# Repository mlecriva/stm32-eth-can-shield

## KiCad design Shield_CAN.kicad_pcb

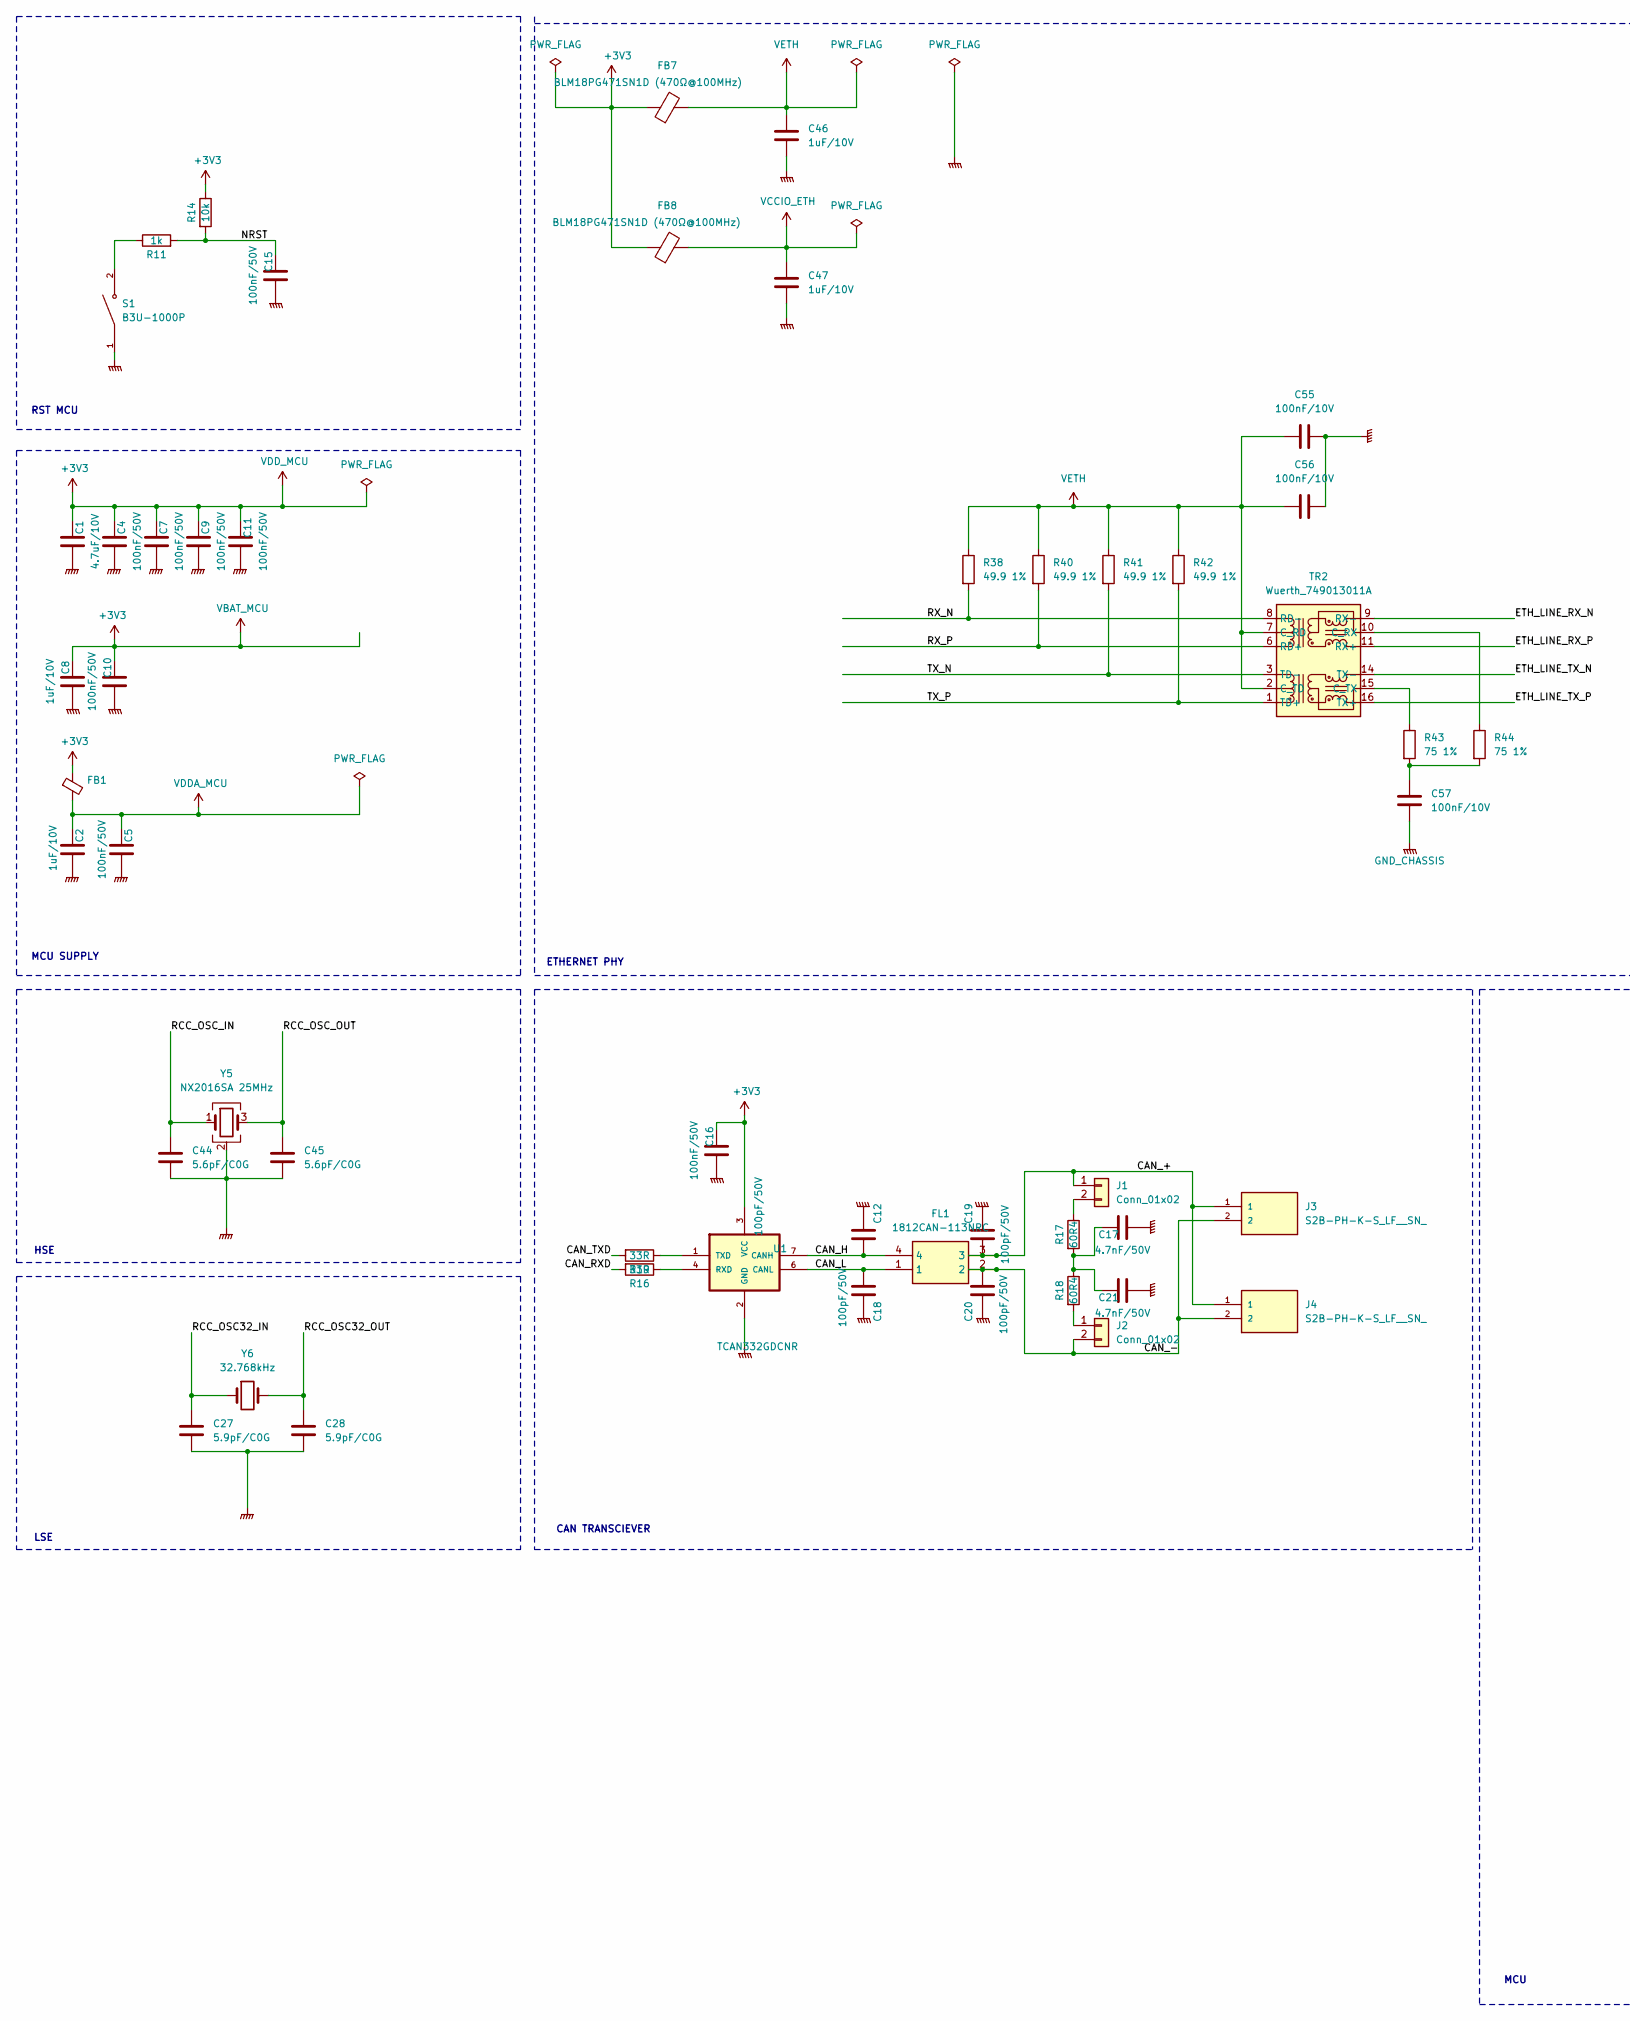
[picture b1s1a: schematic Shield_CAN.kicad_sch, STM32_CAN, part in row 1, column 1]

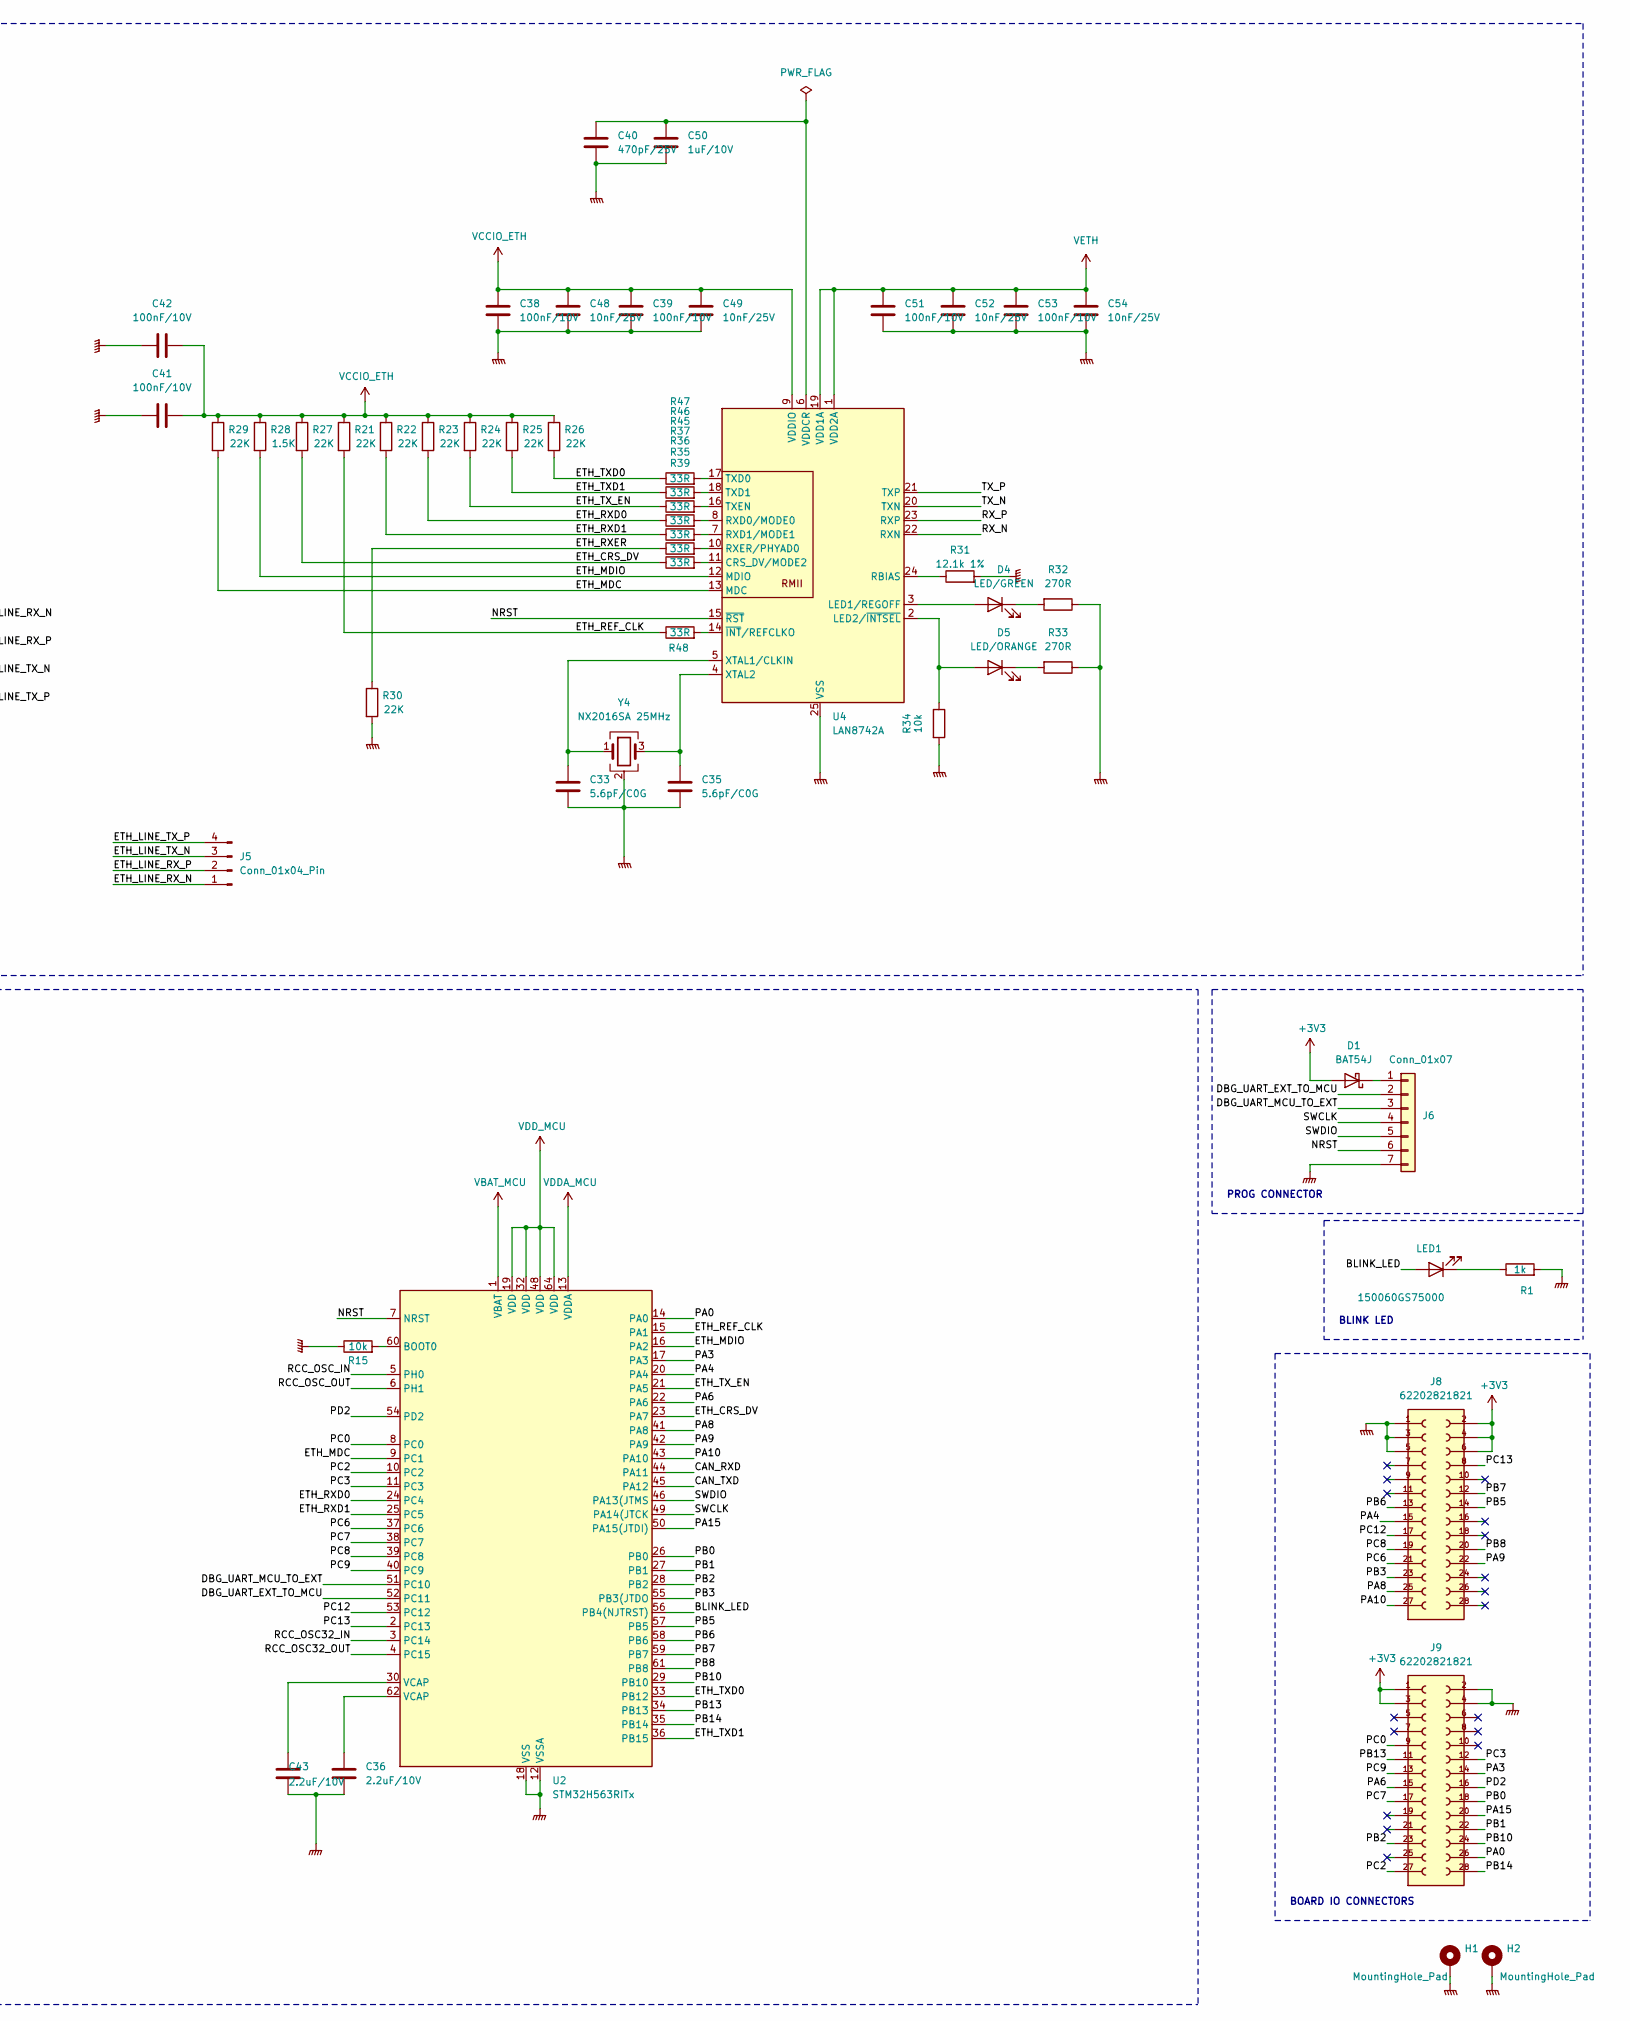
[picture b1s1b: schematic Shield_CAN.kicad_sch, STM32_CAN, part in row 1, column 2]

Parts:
C1: 4.7uF/10V; C_0402_1005Metric; Mfr. Part # GRM155R61A475KEAAD; Digikey_Code 1276-6462-1-ND
C2, C8, C46, C47: 1uF/10V; C_0402_1005Metric; Mfr. Part # CL05A105KP5NNNC; Digikey_Code 445-5138-1-ND
C4, C5, C7, C9, C10, C11, C15, C16: 100nF/50V; C_0402_1005Metric; Mfr. Part # GRM155R71H104KE14D; Digikey_Code 490-GRM155R61H104ME14DCT-ND
C12, C18, C19, C20: 100pF/50V; C_0402_1005Metric; Mfr. Part # C0402C101K5RACAUTO; Digikey_Code 732-7550-1-ND
C17, C21: 4.7nF/50V; C_0402_1005Metric; Mfr. Part # 0402B472K500NT; Digikey_Code 478-KGM05AR71H472KHCT-ND
C27, C28: 5.9pF/C0G; C_0402_1005Metric; Mfr. Part # GJM1555C1H5R9CB01D; LCSC Part # C3846240
C33, C35, C44, C45: 5.6pF/C0G; C_0402_1005Metric; Mfr. Part # GRM1555C1H5R6BA01D; LCSC Part # C76976
C36, C43: 2.2uF/10V; C_0402_1005Metric; Mfr. Part # GRM155Z71A225KE01D; LCSC Part # C2997286
C38, C39, C41, C42, C51, C53, C55, C56, C57: 100nF/10V; C_0402_1005Metric; Mfr. Part # GRM155R71A104KA01D; Digikey_Code 490-GRM155R61H104ME14DCT-ND
C40: 470pF/25V; C_0402_1005Metric; Mfr. Part # CC0402KRX7R8BB471; LCSC Part # C541387
C48, C49, C52, C54: 10nF/25V; C_0402_1005Metric; Mfr. Part # C77013; LCSC Part # C77013
C50: 1uF/10V; C_0402_1005Metric; Mfr. Part # CL05A105KP5NNNC; LCSC Part # C14445
D1: BAT54J; D_SOD-323F; Mfr. Part # BAT54J,115; Digikey_Code 1727-4818-1-ND
D4: LED/GREEN; LED_0603_1608Metric; Mfr. Part # A-SP192DGHC-C01-4T; LCSC Part # C19171301
D5: LED/ORANGE; LED_0603_1608Metric; Mfr. Part # A-SP192DS1C-A01-4T; LCSC Part # C19171353
FB1, FB7: BLM18PG471SN1D (470Ω@100MHz); L_0603_1608Metric; Mfr. Part # BLM18PG600SN1D; Digikey_Code 1934-1469-1-ND
FB8: BLM18PG471SN1D (470Ω@100MHz); L_0603_1608Metric; Mfr. Part # BLM18PG600SN1D; LCSC Part # C85834
FL1: 1812CAN-113NRC; 1812CAN113NRC; Manufacturer_Part_Number 1812CAN-113NRC; Mouser Part Number 994-1812CAN-113NRC
H1, H2: MountingHole_Pad; MountingHole_3mm_Pad
J1, J2: Conn_01x02; PinHeader_1x02_P2.54mm_Vertical; Mfr. Part # P125-1102A0CS116A1; Digikey_Code 732-5315-ND
J3, J4: S2B-PH-K-S_LF__SN_; JST_PH_B2B-PH-K_1x02_P2.00mm_Vertical; Mfr. Part # HDGC2001WV-2P; Digikey_Code 455-1719-ND
J5: Conn_01x04_Pin; Molex_PicoBlade_53047-0410_1x04_P1.25mm_Vertical
J6: Conn_01x07; Molex_PicoBlade_53047-0710_1x07_P1.25mm_Vertical
J8, J9: 62202821821; Mfr. Part # PM127-2-14-Z-4.3-G0; Digikey_Code 732-62202821821-ND
LED1: 150060GS75000; LED_0603_1608Metric; Manufacturer_Part_Number 150060GS75000; Mouser Part Number 710-150060GS75000
R1, R11: 1k; R_0402_1005Metric; Mfr. Part # 0402WGF1001TCE; Digikey_Code YAG3525CT-ND
R14, R15, R34: 10k; R_0402_1005Metric; Mfr. Part # 0402WGF1002TCE; Digikey_Code CR0402-FX-1002GLFCT-ND
R16, R19, R35, R36, R37, R39, R45, R46, R47, R48: 33R; R_0402_1005Metric; Mfr. Part # 0402WGF330JTCE; Digikey_Code 311-33.0LRCT-ND
R17: 60R4; R_0402_1005Metric; Mfr. Part # 0402WGF604JTCE; Digikey_Code 13-RT0805FRE0760R4LCT-ND
R18: 60R4; R_0402_1005Metric; Mfr. Part # 0402WGF604JTCE; Digikey_Code 311-33.0LRCT-ND
R21, R22, R23, R24, R25, R26, R27, R29, R30: 22K; R_0402_1005Metric; Mfr. Part # RC0402FR-0722KL; LCSC Part # C82868
R28: 1.5K; R_0402_1005Metric; Mfr. Part # 0402WGF1501TCE; LCSC Part # C25867
R31: 12.1k 1%; R_0402_1005Metric; Mfr. Part # RTT021212FTH; LCSC Part # C102786
R32, R33: 270R; R_0402_1005Metric; Mfr. Part # CR0402FF2700G; Digikey_Code 311-33.0LRCT-ND
R38, R40, R41, R42: 49.9 1%; R_0402_1005Metric; Mfr. Part # 0402WGF499JTCE; LCSC Part # C25120
R43: 75 1%; R_0402_1005Metric; Mfr. Part # 0402WGF750JTCE; LCSC Part # C25133
R44: 75 1%; R_0402_1005Metric; Mfr. Part # 0402WGF750JTCE; Digikey_Code 311-33.0LRCT-ND
S1: B3U-1000P; SW_B3U-1000P; Mfr. Part # B3U-1000P; LCSC Part # C231329
TR2: Wuerth_749013011A; Transformer_Ethernet_Wuerth_749013011A; Mfr. Part # 749013011A; LCSC Part # C7193798
U1: TCAN332GDCNR; SOT65P280X145-8N; Mfr. Part # TCAN332GDCNR; Digikey_Code 311-33.0LRCT-ND
U2: STM32H563RITx; LQFP-64_10x10mm_P0.5mm; Mfr. Part # STM32H563RIT6; LCSC Part # C20619634
U4: LAN8742A; VQFN-24-1EP_4x4mm_P0.5mm_EP2.5x2.5mm_ThermalVias; Mfr. Part # LAN8742A-CZ-TR; LCSC Part # C621424
Y4, Y5: NX2016SA 25MHz; Crystal_SMD_2016-4Pin_2.0x1.6mm; Mfr. Part # NX2016SA-25MHZ-STD-CZS-2; LCSC Part # C843258
Y6: 32.768kHz; Crystal_SMD_2012-2Pin_2.0x1.2mm_HandSoldering; Mfr. Part # NX2012SA_32.768K_STD-MUB-1; LCSC Part # C500343

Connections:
+3V3: C1.1, C4.1, C7.1, C8.1, C9.1, C10.1, C11.1, C16.1, D1.2 (A), FB1.1, FB7.1, FB8.1, J8.2, J8.4, J8.6, J9.1, J9.3, R14.1, U1.3 (VCC), U2.1 (VBAT), U2.19 (VDD), U2.32 (VDD), U2.48 (VDD), U2.64 (VDD)
/BLINK_LED: LED1.2 (A), U2.56 (PB4(NJTRST))
/CAN_+: C19.1, FL1.3, J1.1, J3.1, J4.1
/CAN_-: C20.1, FL1.2, J2.2, J3.2, J4.2
/CAN_H: C12.1, FL1.4, U1.7 (CANH)
/CAN_L: C18.1, FL1.1, U1.6 (CANL)
/CAN_RXD: R16.2, U2.44 (PA11)
/CAN_TXD: R19.2, U2.45 (PA12)
/DBG_UART_EXT_TO_MCU: J6.2, U2.52 (PC11)
/DBG_UART_MCU_TO_EXT: J6.3, U2.51 (PC10)
/ETH_CRS_DV: R27.2, R47.1, U2.23 (PA7)
/ETH_LINE_RX_N: J5.1, TR2.9 (RX-)
/ETH_LINE_RX_P: J5.2, TR2.11 (RX+)
/ETH_LINE_TX_N: J5.3, TR2.14 (TX-)
/ETH_LINE_TX_P: J5.4, TR2.16 (TX+)
/ETH_MDC: R29.2, U2.9 (PC1), U4.13 (MDC)
/ETH_MDIO: R28.2, U2.16 (PA2), U4.12 (MDIO)
/ETH_REF_CLK: R21.2, R48.1, U2.15 (PA1)
/ETH_RXD0: R23.2, R39.1, U2.24 (PC4)
/ETH_RXD1: R22.2, R45.1, U2.25 (PC5)
/ETH_RXER: R30.1, R46.1
/ETH_TXD0: R26.2, R35.1, U2.33 (PB12)
/ETH_TXD1: R25.2, R36.1, U2.36 (PB15)
/ETH_TX_EN: R24.2, R37.1, U2.21 (PA5)
/NRST: C15.1, J6.6, R11.2, R14.2, U2.7 (NRST), U4.15 (~RST)
/PA0: J9.26, U2.14 (PA0)
/PA3: J9.14, U2.17 (PA3)
/PA4: J8.15, U2.20 (PA4)
/PA6: J9.15, U2.22 (PA6)
/PA8: J8.25, U2.41 (PA8)
/PA9: J8.22, U2.42 (PA9)
/PA10: J8.27, U2.43 (PA10)
/PA15: J9.20, U2.50 (PA15(JTDI))
/PB0: J9.18, U2.26 (PB0)
/PB1: J9.22, U2.27 (PB1)
/PB2: J9.23, U2.28 (PB2)
/PB3: J8.23, U2.55 (PB3(JTDO)
/PB5: J8.14, U2.57 (PB5)
/PB6: J8.13, U2.58 (PB6)
/PB7: J8.12, U2.59 (PB7)
/PB8: J8.20, U2.61 (PB8)
/PB10: J9.24, U2.29 (PB10)
/PB13: J9.11, U2.34 (PB13)
/PB14: J9.28, U2.35 (PB14)
/PC0: J9.9, U2.8 (PC0)
/PC2: J9.27, U2.10 (PC2)
/PC3: J9.12, U2.11 (PC3)
/PC6: J8.21, U2.37 (PC6)
/PC7: J9.17, U2.38 (PC7)
/PC8: J8.19, U2.39 (PC8)
/PC9: J9.13, U2.40 (PC9)
/PC12: J8.17, U2.53 (PC12)
/PC13: J8.8, U2.2 (PC13)
/PD2: J9.16, U2.54 (PD2)
/RCC_OSC32_IN: C27.1, U2.3 (PC14), Y6.1
/RCC_OSC32_OUT: C28.1, U2.4 (PC15), Y6.2
/RCC_OSC_IN: C44.1, U2.5 (PH0), Y5.1
/RCC_OSC_OUT: C45.1, U2.6 (PH1), Y5.3
/RX_N: R38.2, TR2.8 (RD-), U4.22 (RXN)
/RX_P: R40.2, TR2.6 (RD+), U4.23 (RXP)
/SWCLK: J6.4, U2.49 (PA14(JTCK)
/SWDIO: J6.5, U2.46 (PA13(JTMS)
/TX_N: R41.2, TR2.3 (TD-), U4.20 (TXN)
/TX_P: R42.2, TR2.1 (TD+), U4.21 (TXP)
GNDPWR: C1.2, C2.2, C4.2, C5.2, C7.2, C8.2, C9.2, C10.2, C11.2, C12.2, C15.2, C16.2, C17.2, C18.2, C19.2, C20.2, C21.2, C27.2, C28.2, C33.2, C35.2, C36.2, C38.2, C39.2, C40.2, C41.1, C42.1, C43.2, C44.2, C45.2, C46.2, C47.2, C48.2, C49.2, C50.2, C51.2, C52.2, C53.2, C54.2, C55.2, C56.2, H1.1 (1_1), H2.1 (1_1), J6.7, J8.1, J8.3, J8.5, J9.2, J9.4, R1.2, R15.1, R30.2, R31.2, R32.1, R33.1, R34.2, S1.1, U1.2 (GND), U2.12 (VSSA), U2.18 (VSS), U2.31 (VSS), U2.47 (VSS), U2.63 (VSS), U4.25 (VSS), Y4.2 (G), Y4.4 (G), Y5.2 (G), Y5.4 (G)
GND_CHASSIS: C57.1
unnamed: C17.1, C21.1, R17.2, R18.1
unnamed: C36.1, U2.62 (VCAP)
unnamed: C43.1, U2.30 (VCAP)
unnamed: C57.2, R43.2, R44.2
unnamed: D1.1 (K), J6.1
unnamed: D4.2 (A), U4.3 (LED1/REGOFF)
unnamed: D4.1 (K), R32.2
unnamed: D5.2 (A), R34.1, U4.2 (LED2/~INTSEL)
unnamed: D5.1 (K), R33.2
unnamed: J1.2, R17.1
unnamed: J2.1, R18.2
unnamed: LED1.1 (K), R1.1
unnamed: R11.1, S1.2
unnamed: R44.1, TR2.10 (C_RX)
unnamed: R43.1, TR2.15 (C_TX)
unnamed: R16.1, U1.4 (RXD)
unnamed: R19.1, U1.1 (TXD)
unnamed: R15.2, U2.60 (BOOT0)
unnamed: R47.2, U4.11 (CRS_DV/MODE2)
unnamed: R31.1, U4.24 (RBIAS)
unnamed: R39.2, U4.8 (RXD0/MODE0)
unnamed: R45.2, U4.7 (RXD1/MODE1)
unnamed: R46.2, U4.10 (RXER/PHYAD0)
unnamed: R35.2, U4.17 (TXD0)
unnamed: R36.2, U4.18 (TXD1)
unnamed: R37.2, U4.16 (TXEN)
unnamed: C40.1, C50.1, U4.6 (VDDCR)
unnamed: C33.1, U4.5 (XTAL1/CLKIN), Y4.1
unnamed: C35.1, U4.4 (XTAL2), Y4.3
unnamed: R48.2, U4.14 (~INT/REFCLKO)
VCCIO_ETH: C38.1, C39.1, C41.2, C42.2, C47.1, C48.1, C49.1, FB8.2, R21.1, R22.1, R23.1, R24.1, R25.1, R26.1, R27.1, R28.1, R29.1, U4.9 (VDDIO)
VDDA_MCU: C2.1, C5.1, FB1.2, U2.13 (VDDA)
VETH: C46.1, C51.1, C52.1, C53.1, C54.1, C55.1, C56.1, FB7.2, R38.1, R40.1, R41.1, R42.1, TR2.2 (C_TD), TR2.7 (C_RD), U4.1 (VDD2A), U4.19 (VDD1A)

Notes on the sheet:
MCU
HSE
BLINK LED
CAN TRANSCIEVER
RST MCU
BOARD IO CONNECTORS
ETHERNET PHY
LSE
PROG CONNECTOR
MCU SUPPLY

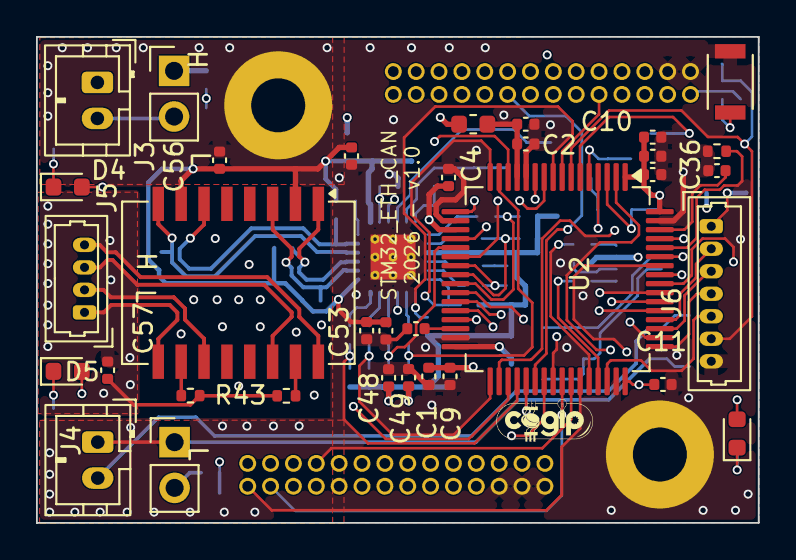
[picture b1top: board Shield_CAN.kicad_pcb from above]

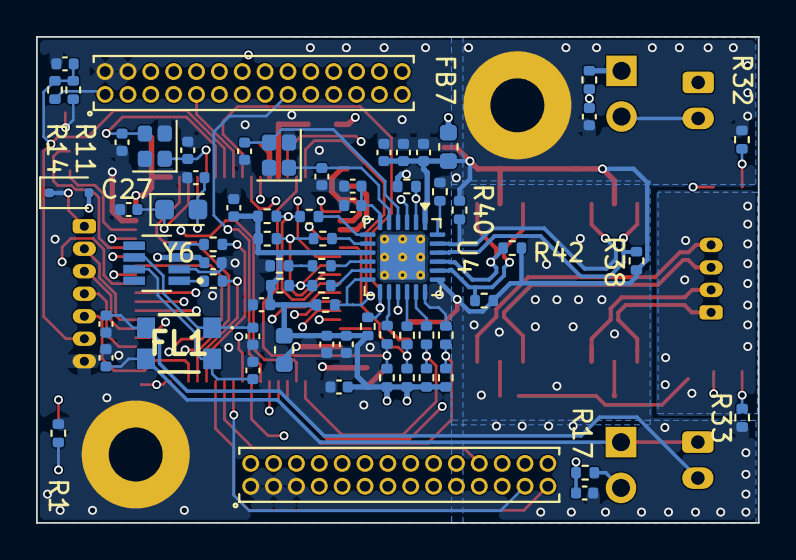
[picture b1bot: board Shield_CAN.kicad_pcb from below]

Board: 4 copper layers, 40.1 x 27.0 mm, 104 parts (68 on the bottom side), 98 nets.

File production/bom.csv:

Designator,Footprint,Quantity,Value,LCSC Part #
C1,0402,1,4.7uF/10V,C77004
"C10, C11, C15, C16, C4, C5, C7, C9",0402,8,100nF/50V,C77020
"C12, C18, C19, C20",0402,4,100pF/50V,C141051
"C17, C21",0402,2,4.7nF/50V,C1538
"C2, C46, C47, C50, C8",0402,5,1uF/10V,C14445
"C27, C28",0402,2,5.9pF/C0G,C3846240
"C33, C35, C44, C45",0402,4,5.6pF/C0G,C76976
"C36, C43",0402,2,2.2uF/10V,C2997286
"C38, C39, C41, C42, C51, C53, C55, C56, C57",0402,9,100nF/10V,C71687
C40,0402,1,470pF/25V,C541387
"C48, C49, C52, C54",0402,4,10nF/25V,C77013
D1,D_SOD-323F,1,BAT54J,C130415
D4,0603,1,LED/GREEN,C19171301
D5,0603,1,LED/ORANGE,C19171353
"FB1, FB7, FB8",0603,3,BLM18PG471SN1D (470Ω@100MHz),C85834
FL1,1812CAN113NRC,1,1812CAN-113NRC,C391261
"J1, J2",PinHeader_1x02_P2.54mm_Vertical,2,Conn_01x02,C7494857
"J3, J4",JST_PH_B2B-PH-K_1x02_P2.00mm_Vertical,2,S2B-PH-K-S_LF__SN_,C5175230
J5,Molex_PicoBlade_53047-0410_1x04_P1.25mm_Vertical,1,Conn_01x04_Pin,
J6,Molex_PicoBlade_53047-0710_1x07_P1.25mm_Vertical,1,Conn_01x07,
"J8, J9",62202821821,2,62202821821,C5380283
LED1,0603,1,150060GS75000,C19171301
"R1, R11",0402,2,1k,C11702
"R14, R15, R34",0402,3,10k,C25744
"R16, R19, R35, R36, R37, R39, R45, R46, R47, R48",0402,10,33R,C25105
"R17, R18",0402,2,60R4,C60310
"R21, R22, R23, R24, R25, R26, R27, R29, R30",0402,9,22K,C82868
R28,0402,1,1.5K,C25867
R31,0402,1,12.1k 1%,C102786
"R32, R33",0402,2,270R,C100346
"R38, R40, R41, R42",0402,4,49.9 1%,C25120
"R43, R44",0402,2,75 1%,C25133
S1,SW_B3U-1000P,1,B3U-1000P,C231329
TR2,Transformer_Ethernet_Wuerth_749013011A,1,Wuerth_749013011A,C7193798
U1,SOT65P280X145-8N,1,TCAN332GDCNR,C191007
U2,LQFP-64_10x10mm_P0.5mm,1,STM32H563RITx,C20619634
U4,VQFN-24-1EP_4x4mm_P0.5mm_EP2.5x2.5mm_ThermalVias,1,LAN8742A,C621424
"Y4, Y5",Crystal_SMD_2016-4Pin_2.0x1.6mm,2,NX2016SA 25MHz,C843258
Y6,Crystal_SMD_2012-2Pin_2.0x1.2mm_HandSoldering,1,32.768kHz,C500343

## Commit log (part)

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2026-06-24 initial commit
    full connector routed
